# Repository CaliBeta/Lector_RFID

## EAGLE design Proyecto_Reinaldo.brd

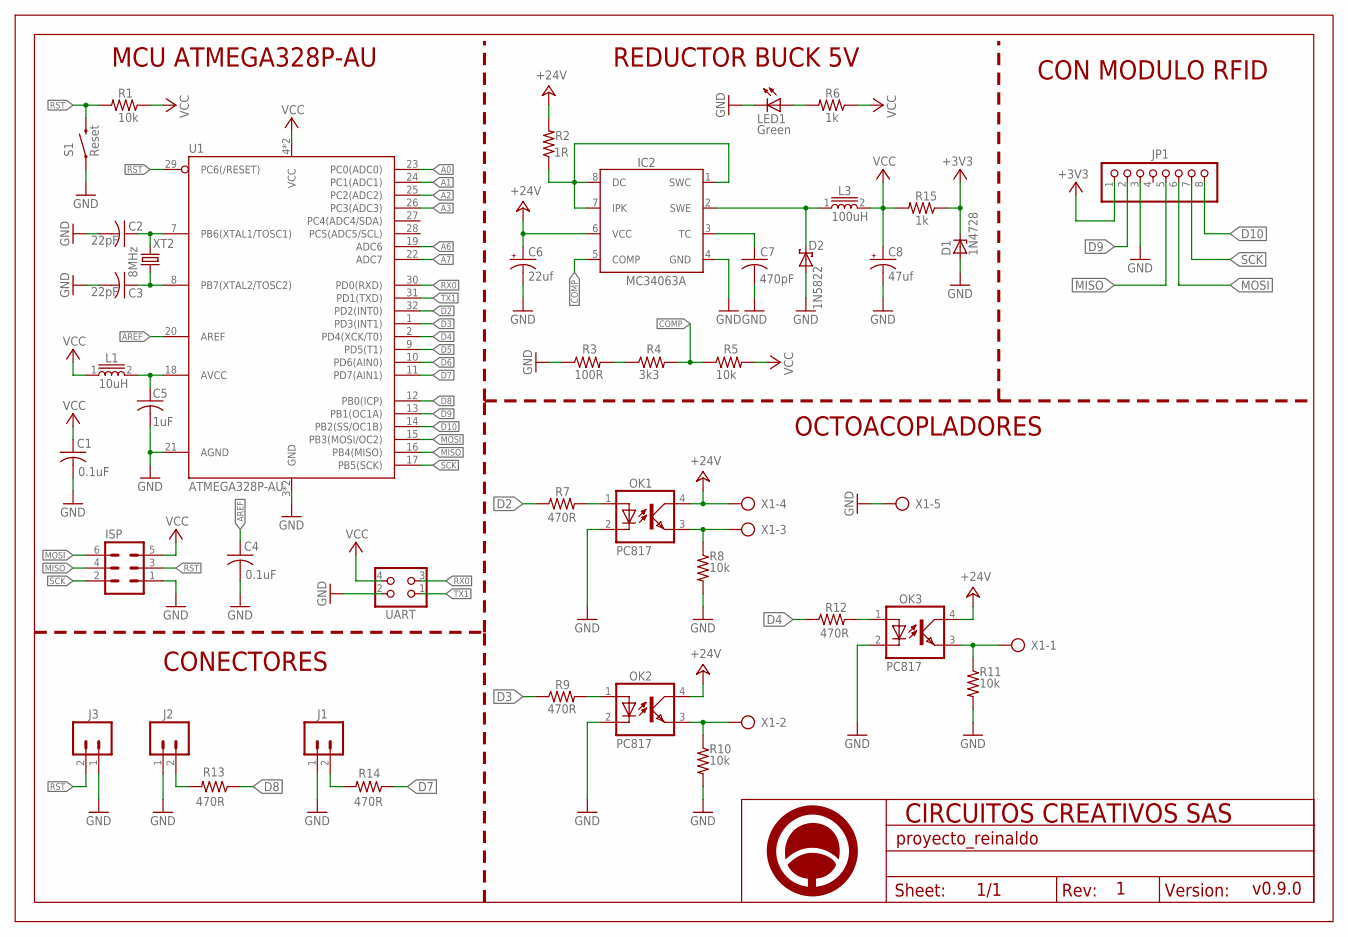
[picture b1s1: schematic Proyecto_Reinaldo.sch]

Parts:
C1, C4: 0.1uF; C0805
C2, C3: 22pF; C0805
C5: 1uF; C0805
C6: 22uf; E2,5-6E
C7: 470pF; C0805
C8: 47uf; E2,5-6E
D1: 1N4728; DO41Z10
D2: 1N5822; DO-214AC
IC2: MC34063A; SOIC-8
ISP: MA03-2
J1, J2, J3: M02LOCK; 1X02_LOCK
JP1: PINHD-1X8BIG; 1X08-BIG
L1: 10uH; L0805
L3: 100uH; CD54
LED1: Green; CHIPLED_0805
OK1, OK2, OK3: PC817; DIL04
R1, R5, R8, R10, R11: 10k; R1206
R2: 1R; R1206
R3: 100R; R1206
R4: 3k3; R1206
R6, R15: 1k; R1206
R7, R9, R12, R13, R14: 470R; R1206
S1: Reset; TACTILE-SWITCH-1101NE
U1: ATMEGA328P-AU; TQFP32
U$1: A4_HORIZONTAL; LOGO
UART: IPS_CIRCUITOS; ISP_CIRCUITOS
X1: AK500/5
XT2: 8MHz; SM49

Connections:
+3V3: D1.C, JP1.1, R15.1
+24V: C6.+, IC2.6 (VCC), OK1.4 (COL), OK2.4 (COL), OK3.4 (COL), R2.2, X1.4
A0: U1.23 (PC0(ADC0))
A1: U1.24 (PC1(ADC1))
A2: U1.25 (PC2(ADC2))
A3: U1.26 (PC3(ADC3))
A6: U1.19 (ADC6)
A7: U1.22 (ADC7)
AREF: C4.1, U1.20 (AREF)
COMP: IC2.5 (COMP), R4.2, R5.1
D2: R7.1, U1.32 (PD2(INT0))
D3: R9.1, U1.1 (PD3(INT1))
D4: R12.1, U1.2 (PD4(XCK/T0))
D5: U1.9 (PD5(T1))
D6: U1.10 (PD6(AIN0))
D7: R14.1, U1.11 (PD7(AIN1))
D8: R13.1, U1.12 (PB0(ICP))
D9: JP1.2, U1.13 (PB1(OC1A))
D10: JP1.8, U1.14 (PB2(SS/OC1B))
GND: C1.2, C2.2, C3.2, C4.2, C5.2, C6.-, C7.2, C8.-, D1.A, D2.A, IC2.4 (GND), ISP.1, J1.1, J2.1, J3.1, JP1.3, LED1.C, OK1.2 (C), OK2.2 (C), OK3.2 (C), R3.1, R8.2, R10.2, R11.2, S1.P$1 (1), U1.3 (GND), U1.5 (GND), U1.21 (AGND), UART.2, X1.5
MISO: ISP.4, JP1.5, U1.16 (PB4(MISO))
MOSI: ISP.6, JP1.6, U1.15 (PB3(MOSI/OC2))
unnamed: OK1.1 (A), R7.2
unnamed: OK2.1 (A), R9.2
unnamed: OK3.1 (A), R12.2
unnamed: J2.2, R13.2
unnamed: J1.2, R14.2
unnamed: LED1.A, R6.2
unnamed: C7.1, IC2.3 (TC)
unnamed: IC2.1 (SWC), IC2.7 (IPK), IC2.8 (DC), R2.1
unnamed: R3.2, R4.1
unnamed: C5.1, L1.2, U1.18 (AVCC)
unnamed: D2.K, IC2.2 (SWE), L3.1
OK1: OK1.3 (EMIT), R8.1, X1.3
OK2: OK2.3 (EMIT), R10.1, X1.2
OK3: OK3.3 (EMIT), R11.1, X1.1
OS1: C2.1, U1.7 (PB6(XTAL1/TOSC1)), XT2.2
OS2: C3.1, U1.8 (PB7(XTAL2/TOSC2)), XT2.1
RST: ISP.3, J3.2, R1.2, S1.P$2 (2), U1.29 (PC6(/RESET))
RX0: U1.30 (PD0(RXD)), UART.3
SCK: ISP.2, JP1.7, U1.17 (PB5(SCK))
TX1: U1.31 (PD1(TXD)), UART.1
VCC: C1.1, C8.+, ISP.5, L1.1, L3.2, R1.1, R5.2, R6.1, R15.2, U1.4 (VCC), U1.6 (VCC), UART.4

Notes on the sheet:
v0.9.0
REDUCTOR BUCK 5V
MCU ATMEGA328P-AU
CON MODULO RFID
CONECTORES
OCTOACOPLADORES

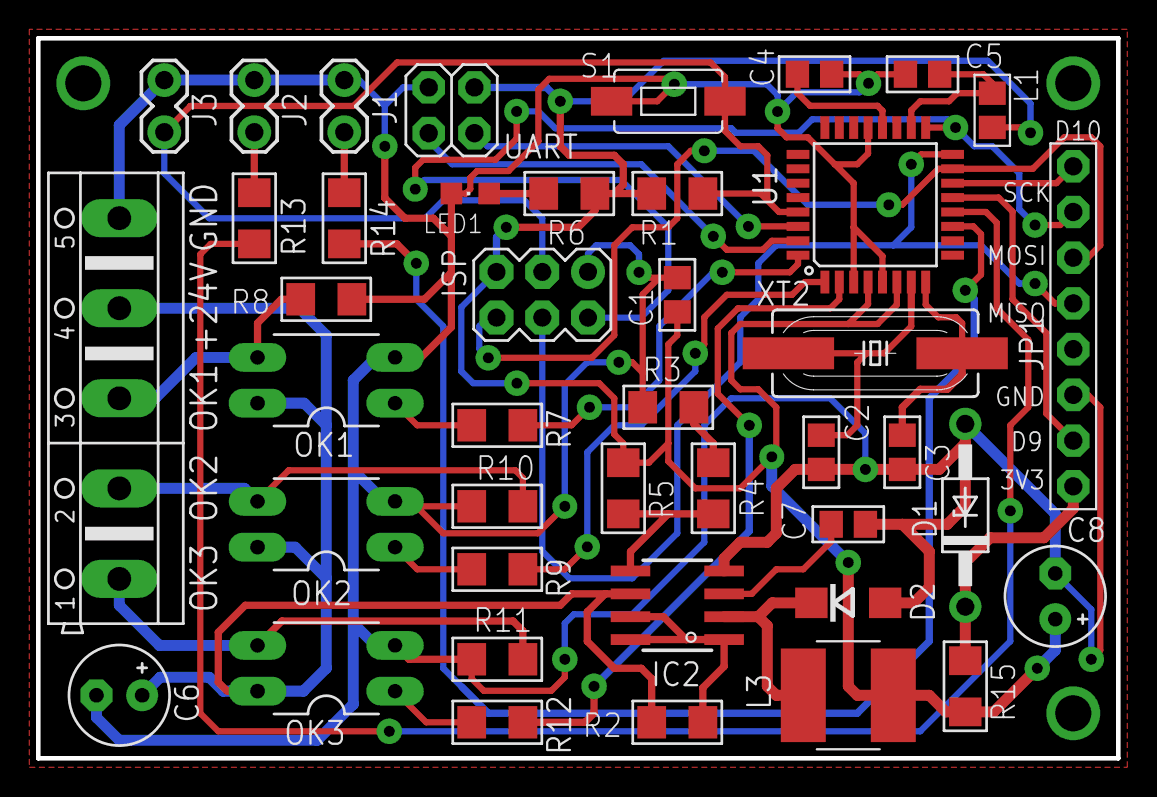
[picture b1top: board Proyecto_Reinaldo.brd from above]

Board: 2 copper layers, 60.0 x 40.0 mm, 43 parts (1 on the bottom side), 35 nets.

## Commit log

2019-07-12 Commit inicial, corrigiendo SCH y BRD Andersson
2019-07-15 Terminado posicionado componentes BRD
2019-07-15 Ruteo BRD al 68%
2019-07-15 Terminado BRD, inicio revision
2019-07-23 Generado archivos de fabricacion
2019-07-23 Eliminado aechivos svg, eran muy pesados

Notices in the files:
parts and their libraries:
SparkFun-Connectors: Licensing: Creative Commons ShareAlike 4.0 International - https://creativecommons.org/licenses/by-sa/4.0
